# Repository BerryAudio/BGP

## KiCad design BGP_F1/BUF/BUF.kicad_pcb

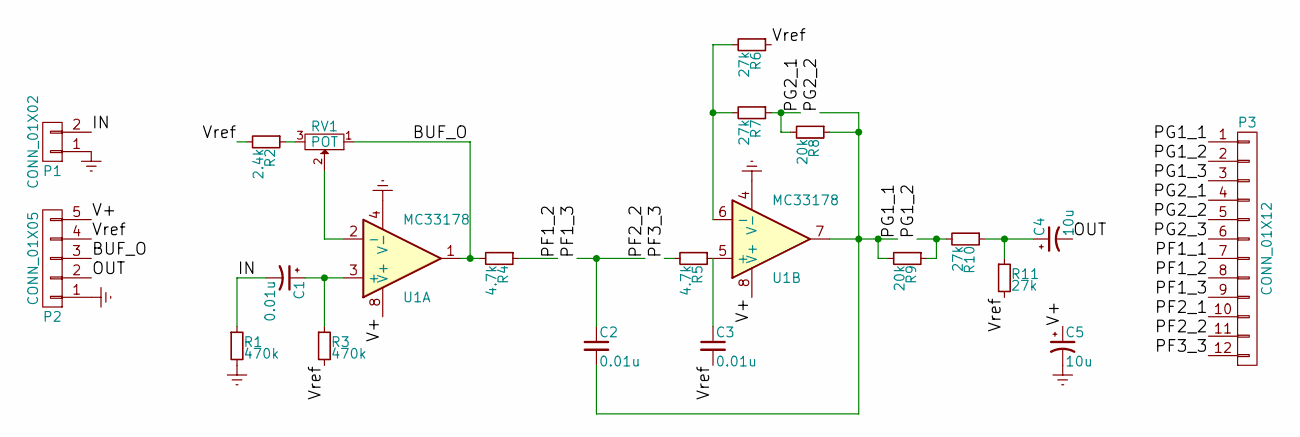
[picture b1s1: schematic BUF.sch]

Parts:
C1: 0.01u; TantalC_SizeR_EIA-2012
C2, C3: 0.01u; C_0805_HandSoldering
C4, C5: 10u; TantalC_SizeR_EIA-2012
P1: CONN_01X02; TerminalBlock_Pheonix_MPT-2.54mm_2pol
P2: CONN_01X05; JST_PH_B5B-PH-K_05x2.00mm_Straight
P3: CONN_01X12; Potentiometer_Alps_RK097_Quad_Vertical_Dual_Shaft
R1, R3: 470k; R_0603_HandSoldering
R2: 2.4k; R_0603_HandSoldering
R4, R5: 4.7k; R_0603_HandSoldering
R6, R7, R10, R11: 27k; R_0603_HandSoldering
R8, R9: 20k; R_0603_HandSoldering
RV1: POT; Potentiometer_Trimmer_Bourns_3296X
U1: MC33178; SOIC-8_3.9x4.9mm_Pitch1.27mm

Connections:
/BUF_O: P2.3, R4.2, RV1.1, U1.1
/IN: C1.2, P1.2, R1.1
/OUT: C4.2, P2.2
/PF1_1: P3.7
/PF1_2: P3.8, R4.1
/PF1_3: C2.1, P3.9, P3.11
/PF2_1: P3.10
/PF3_3: P3.12, R5.2
/PG1_1: C2.2, P3.1, P3.5, R8.1, R9.2, U1.7
/PG1_2: P3.2, R9.1, R10.2
/PG1_3: P3.3
/PG2_1: P3.4, R7.1, R8.2
/PG2_3: P3.6
/V+: C5.1, P2.5, U1.8 (V+)
/Vref: C3.2, P2.4, R2.2, R3.2, R6.1, R11.2
Earth: C5.2, P1.1, P2.1, R1.2, U1.4 (V-)
unnamed: C1.1, R3.1, U1.3 (+)
unnamed: C3.1, R5.1, U1.5 (+)
unnamed: C4.1, R10.1, R11.1
unnamed: R2.1, RV1.3
unnamed: R6.2, R7.2, U1.6 (-)
unnamed: RV1.2, U1.2 (-)

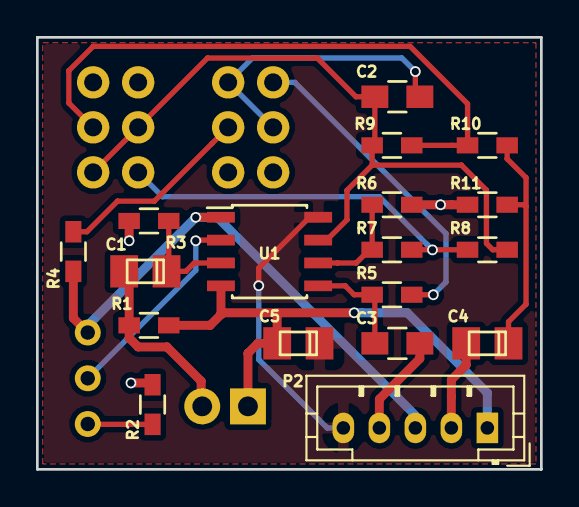
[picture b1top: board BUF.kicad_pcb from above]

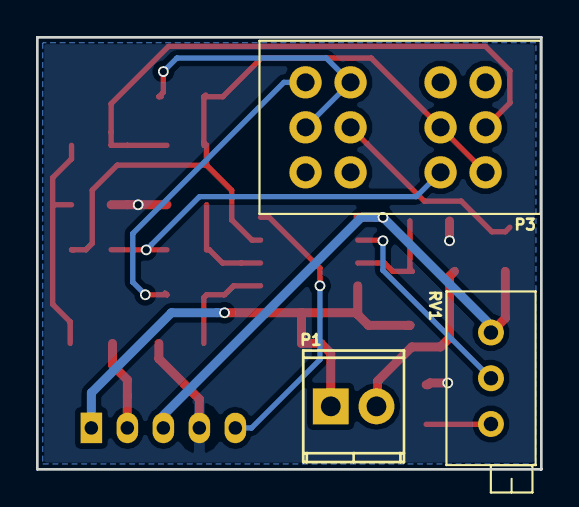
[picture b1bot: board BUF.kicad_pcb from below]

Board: 2 copper layers, 28.0 x 24.0 mm, 21 parts (3 on the bottom side), 18 nets.

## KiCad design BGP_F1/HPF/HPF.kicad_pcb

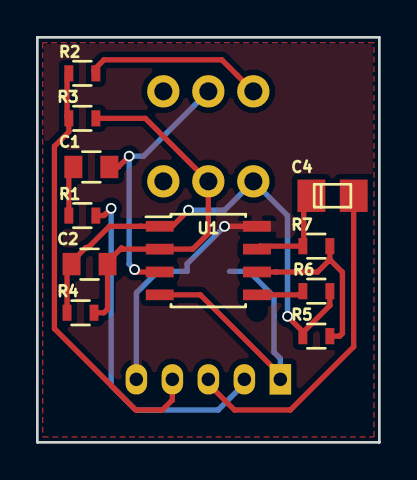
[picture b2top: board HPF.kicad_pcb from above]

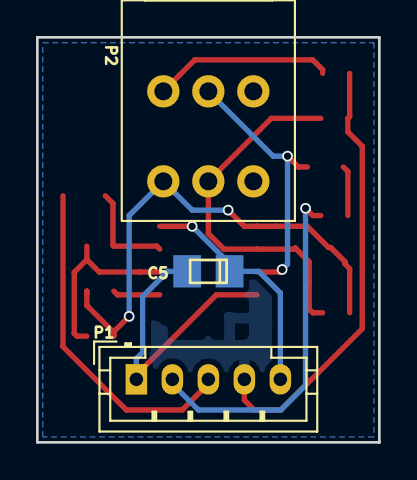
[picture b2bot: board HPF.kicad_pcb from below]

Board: 2 copper layers, 19.0 x 22.5 mm, 14 parts (3 on the bottom side), 13 nets.

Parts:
C1: 2.7n; C_0805
C2: 100p; C_0805
C4, C5: 10u; TantalC_SizeR_EIA-2012
P1: CONN_01X05; JST_PH_B5B-PH-K_05x2.00mm_Straight
P2: CONN_01X06; Potentiometer_Alps_RK097_Double_Vertical_Dual_Shaft
R1: 100; R_0603
R2: 10k; R_0603
R3, R5, R7: 4.7k; R_0603
R4: 24k; R_0603
R6: 47k; R_0603
U1: MC33178; SOIC-8_3.9x4.9mm_Pitch1.27mm

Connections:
/BUF_I: P1.2, R1.2
/OUT: C4.2, P1.3
/V+: C5.1, P1.5, U1.8
/VF_2: C1.1, P2.2, U1.3
/VF_3: P2.3, R2.2
/VG_2: C2.2, P2.5, R3.2, R4.2, U1.2
/VG_3: C2.1, P2.6, R4.1, R5.2, R6.2, U1.1
/Vref: P1.4, R2.1, R3.1
Earth: C5.2, P1.1, U1.4
unnamed: C1.2, R1.1
unnamed: R6.1, U1.5
unnamed: C4.1, R7.1, U1.7
unnamed: R5.1, R7.2, U1.6

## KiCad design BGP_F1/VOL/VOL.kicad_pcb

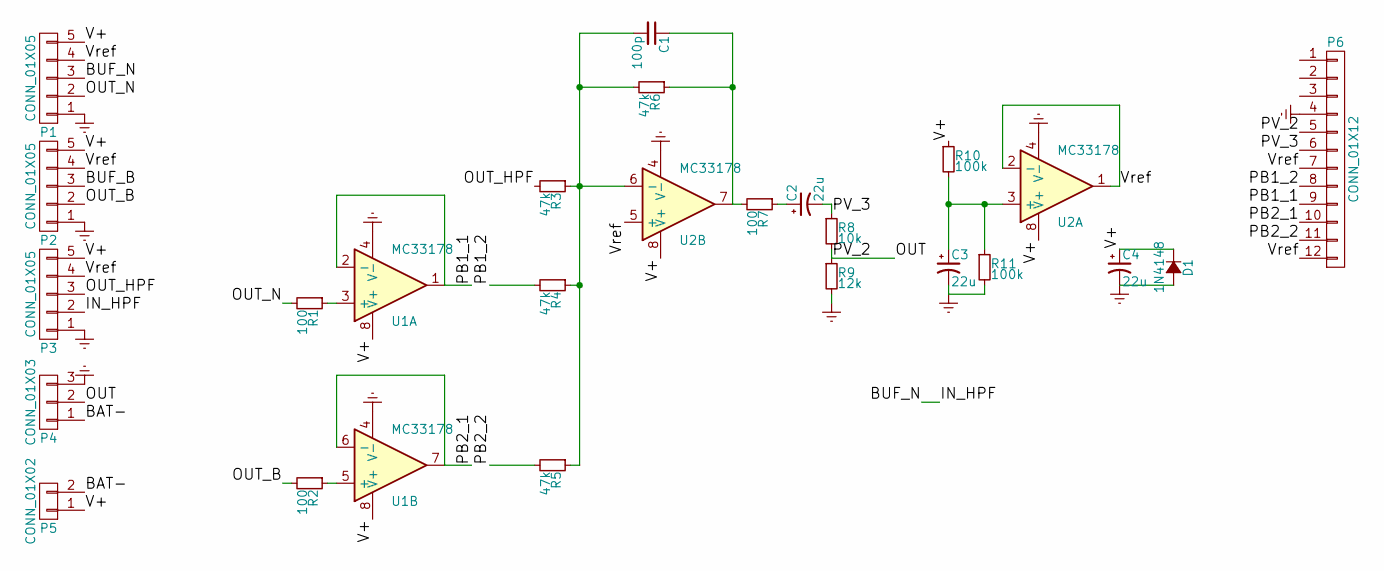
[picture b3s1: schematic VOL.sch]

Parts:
C1: 100p; C_0805
C2, C3, C4: 22u; TantalC_SizeS_EIA-3216
D1: 1N4148; SOD-123
P1: CONN_01X05; SMA_Standard
P2, P3: CONN_01X05; JST_PH_B5B-PH-K_05x2.00mm_Straight
P4: CONN_01X03; TerminalBlock_Pheonix_MPT-2.54mm_3pol
P5: CONN_01X02; TerminalBlock_Pheonix_MPT-2.54mm_2pol
P6: CONN_01X12; Potentiometer_Alps_RK097_Quad_Vertical_Dual_Shaft
R1, R2, R7: 100; R_0603
R3, R4, R5, R6: 47k; R_0603
R8: 10k; R_0603
R9: 12k; R_0603
R10, R11: 100k; R_0603
U1, U2: MC33178; SOIC-8_3.9x4.9mm_Pitch1.27mm

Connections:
/BAT-: P4.1, P5.2
/BUF_B: P2.3
/BUF_N: P1.3, P3.2
/OUT: P4.2, P6.5, R8.2, R9.1
/OUT_B: P2.2, R2.2
/OUT_HPF: P3.3, R3.2
/OUT_N: P1.2, R1.2
/PB1_1: P6.9, U1.1, U1.2 (-)
/PB1_2: P6.8, R4.2
/PB2_1: P6.10, U1.6 (-), U1.7
/PB2_2: P6.11, R5.2
/PV_3: C2.2, P6.6, R8.1
/V+: C4.1, D1.1 (K), P1.5, P2.5, P3.5, P5.1, R10.1, U1.8 (V+), U2.8 (V+)
/Vref: P1.4, P2.4, P3.4, P6.7, P6.12, U2.1, U2.2 (-), U2.5 (+)
Earth: C3.2, C4.2, D1.2 (A), P1.1, P2.1, P3.1, P4.3, P6.4, R9.2, R11.2, U1.4 (V-), U2.4 (V-)
unnamed: C1.1, R6.1, R7.2, U2.7
unnamed: C1.2, R3.1, R4.1, R5.1, R6.2, U2.6 (-)
unnamed: C2.1, R7.1
unnamed: C3.1, R10.2, R11.1, U2.3 (+)
unnamed: R1.1, U1.3 (+)
unnamed: R2.1, U1.5 (+)

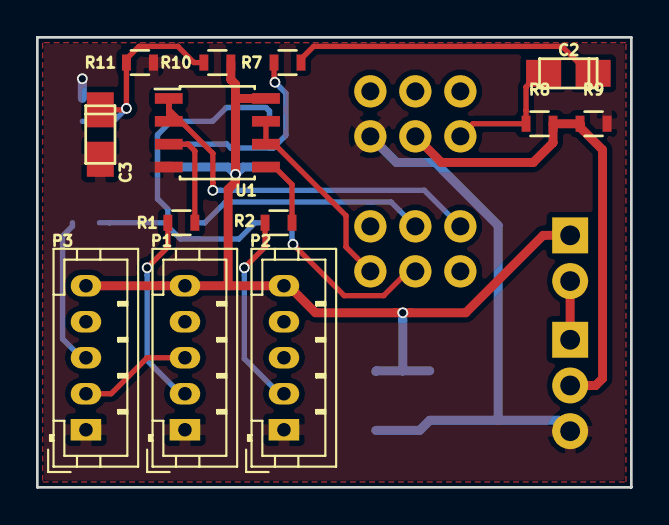
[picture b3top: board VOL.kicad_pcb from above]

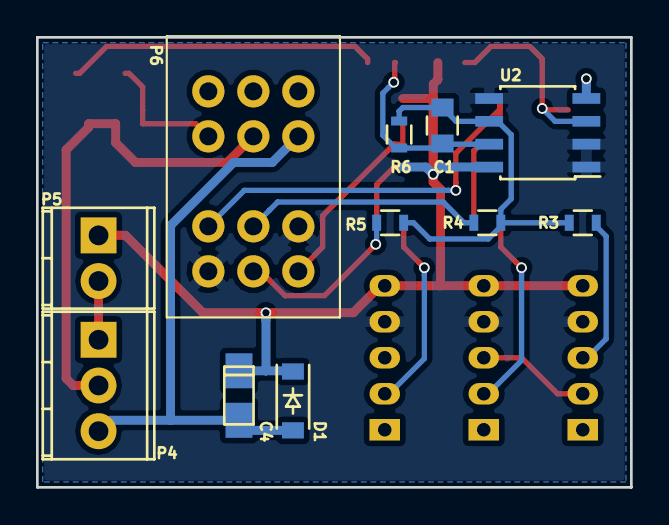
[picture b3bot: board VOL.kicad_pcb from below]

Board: 2 copper layers, 33.0 x 25.0 mm, 24 parts (11 on the bottom side), 20 nets.

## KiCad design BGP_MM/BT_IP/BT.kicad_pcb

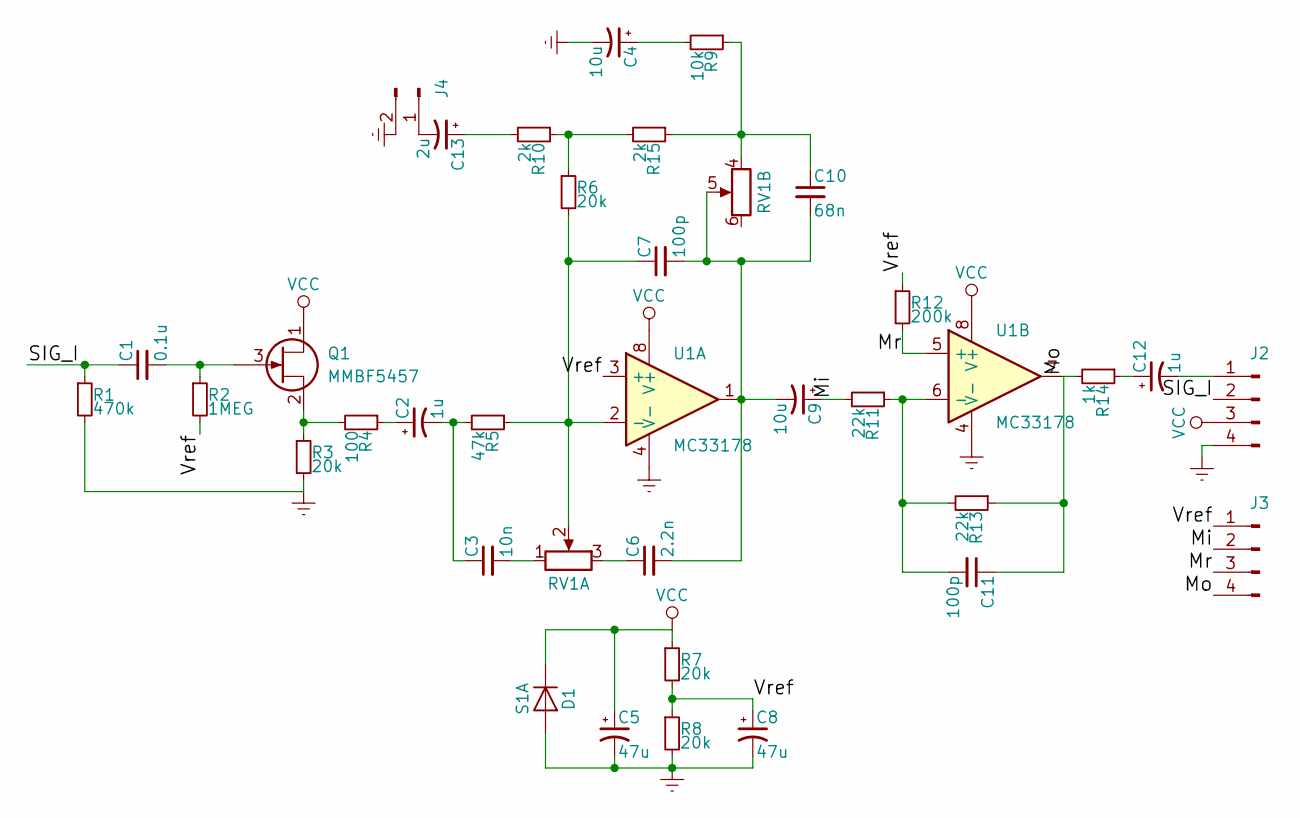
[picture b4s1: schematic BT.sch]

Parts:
C1: 0.1u; C_0805
C2, C12: 1u; C_0805
C3: 10n; C_Rect_L4.6mm_W3.0mm_P2.50mm_MKS02_FKP02
C4: 10u; C_1206_HandSoldering
C5: 47u; C_1206_HandSoldering
C6: 2.2n; C_0805
C7, C11: 100p; C_0603
C8: 47u; C_1206
C9: 10u; C_1206
C10: 68n; C_Rect_L4.6mm_W3.0mm_P2.50mm_MKS02_FKP02
C13: 2u; C_0805
D1: S1A; D_SMA
J2, J3: Conn_01x04_Male; JST_PH_B4B-PH-K_04x2.00mm_Straight
J4: Conn_01x02_Male; JST_PH_B2B-PH-K_02x2.00mm_Straight
Q1: MMBF5457; SOT-23
R1: 470k; R_0603
R2: 1MEG; R_0603
R3, R6, R7, R8: 20k; R_0603
R4: 100; R_0603
R5: 47k; R_0603
R9: 10k; R_0603
R10, R15: 2k; R_0603
R11, R13: 22k; R_0603
R12: 200k; R_0603
R14: 1k; R_0603
RV1: POT_MM_DUAL; Potentiometer_Alpha_Double_Vertical_Dual_Shaft
U1: MC33178; SOIC-8-N

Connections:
/Mi: C9.1, J3.2, R11.2
/Mo: C11.1, J3.4, R13.1, R14.2, U1.7
/Mr: J3.3, R12.2, U1.5 (+)
/SIG_I: C1.1, J2.2, R1.1
/Vref: C8.1, J3.1, R2.2, R7.2, R8.1, R12.1, U1.3 (+)
Earth: C4.2, C5.2, C8.2, D1.2 (A), J2.4, J4.2, R1.2, R3.2, R8.2, U1.4 (V-)
unnamed: C1.2, Q1.3 (G), R2.1
unnamed: C2.1, R4.1
unnamed: C2.2, C3.1, R5.2
unnamed: C3.2, RV1.1 (4)
unnamed: C4.1, R9.2
unnamed: C6.1, RV1.3 (6)
unnamed: C7.1, R5.1, R6.2, RV1.2 (5), U1.2 (-)
unnamed: C10.1, R9.1, R15.1, RV1.4
unnamed: C6.2, C7.2, C9.2, C10.2, RV1.5, U1.1
unnamed: C11.2, R11.1, R13.2, U1.6 (-)
unnamed: C12.1, R14.1
unnamed: C12.2, J2.1
unnamed: C13.1, R10.2
unnamed: C13.2, J4.1
unnamed: Q1.2 (S), R3.1, R4.2
unnamed: R6.1, R10.1, R15.2
VCC: C5.1, D1.1 (K), J2.3, Q1.1 (D), R7.1, U1.8 (V+)

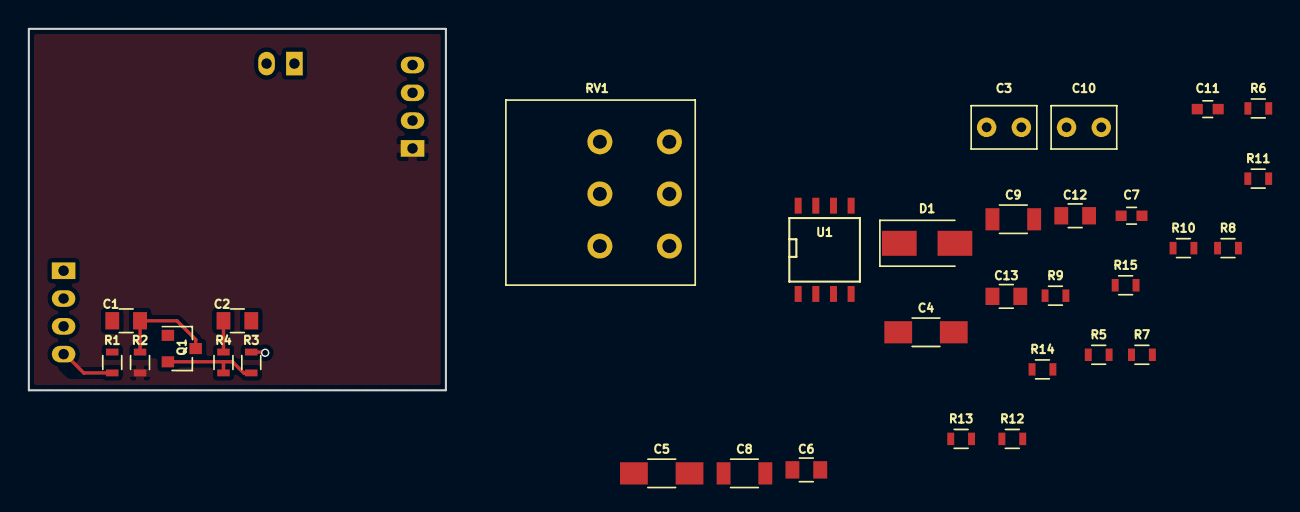
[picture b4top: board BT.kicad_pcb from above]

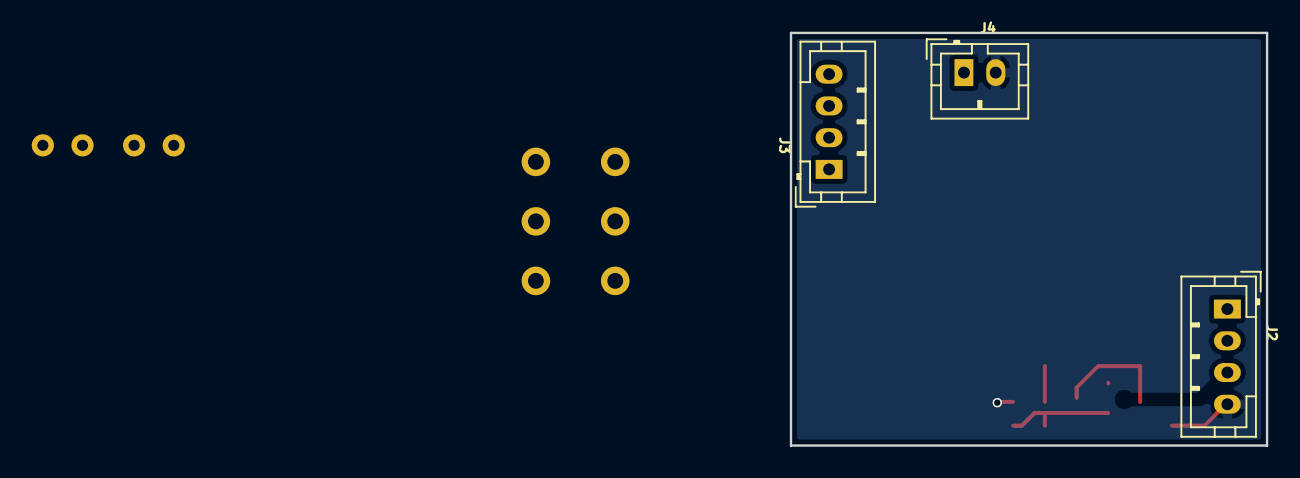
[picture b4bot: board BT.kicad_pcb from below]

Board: 2 copper layers, 30.0 x 26.0 mm, 35 parts (3 on the bottom side), 23 nets.

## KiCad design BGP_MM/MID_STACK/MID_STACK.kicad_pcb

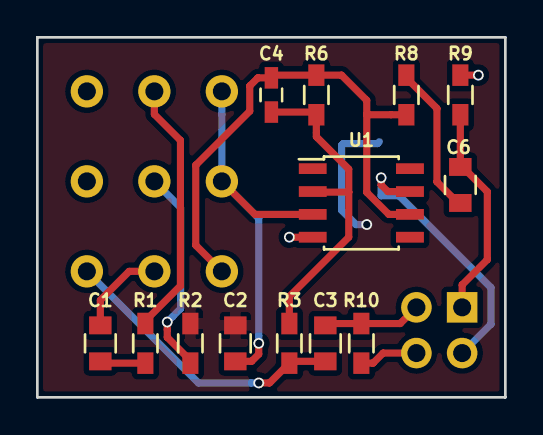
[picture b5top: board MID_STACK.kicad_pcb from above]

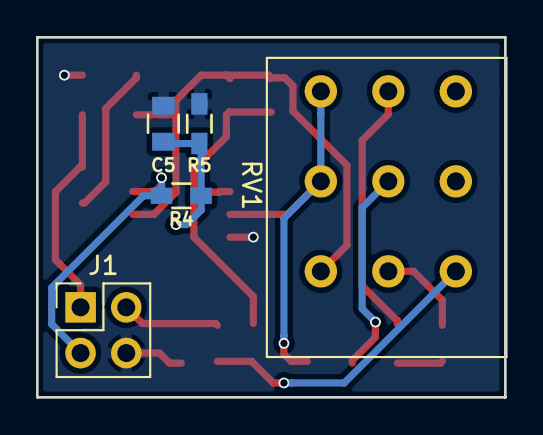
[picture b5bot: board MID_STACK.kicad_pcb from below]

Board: 2 copper layers, 26.0 x 20.0 mm, 18 parts (5 on the bottom side), 14 nets.

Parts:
C1: 10n; C_0805
C2: 4.7n; C_0805
C3, C5, C6: 10u; C_0805
C4: 120p; C_0603_HandSoldering
J1: Conn_01x04_Male; Pin_Header_Straight_2x02_Pitch2.54mm
R1, R2: 10k; R_0603_HandSoldering
R3, R6: 20k; R_0603_HandSoldering
R4, R5, R9, R10: 100k; R_0603_HandSoldering
R8: 1k; R_0603_HandSoldering
RV1: CONN_01X09; Potentiometer_Alpha_Tripple_Vertical_Dual_Shaft
U1: TL061; SOIC-8_3.9x4.9mm_Pitch1.27mm

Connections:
/F1_2: R1.2, RV1.2
/F2_2: R2.1, RV1.5
/IN: C3.2, J1.2, R10.1
/MID_I: C3.1, R3.1, RV1.7
/MID_O: C4.1, R6.2, R8.1, RV1.9, U1.6
/MID_R: C2.1, RV1.3, RV1.6, U1.3
/OUT: C6.2, J1.1, R9.1
/VOL2: C1.1, RV1.8
/Vref: C2.2, C5.1, R2.2, R4.2, R5.1
Earth: C5.2, J1.4, R5.2, R9.2, R10.2, U1.4
unnamed: C1.2, R1.1
unnamed: C4.2, R3.2, R6.1, U1.2
unnamed: C6.1, R8.2
VCC: J1.3, R4.1, U1.7

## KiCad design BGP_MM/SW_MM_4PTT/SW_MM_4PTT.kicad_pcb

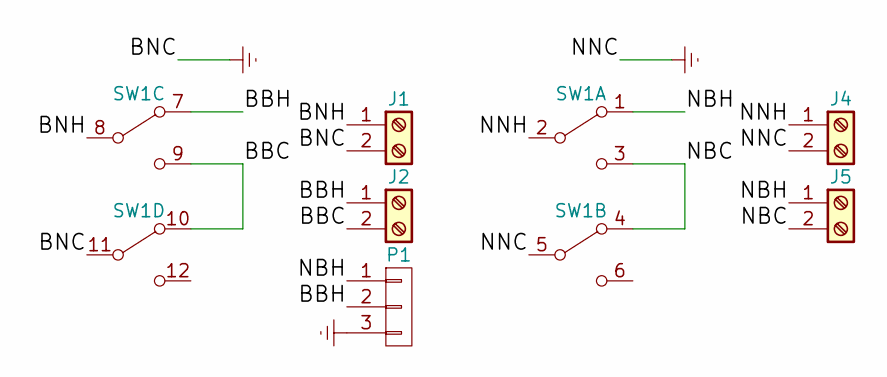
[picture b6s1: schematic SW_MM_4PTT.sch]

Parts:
J1, J2, J4, J5: Screw_Terminal_01x02; TerminalBlock_Phoenix_MPT-2.54mm_2pol
P1: CONN_01X03; JST_PH_B3B-PH-K_03x2.00mm_Straight
SW1: SW_4PDT_x4; NKK_DP3T

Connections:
/BBC: J2.2, SW1.9 (C), SW1.10 (A)
/BBH: J2.1, P1.2, SW1.7 (A)
/BNH: J1.1, SW1.8 (B)
/NBC: J5.2, SW1.3 (C), SW1.4 (A)
/NBH: J5.1, P1.1, SW1.1 (A)
/NNH: J4.1, SW1.2 (B)
Earth: J1.2, J4.2, P1.3, SW1.5 (B), SW1.11 (B)

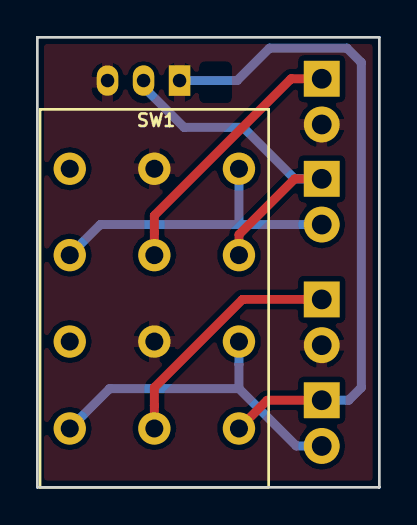
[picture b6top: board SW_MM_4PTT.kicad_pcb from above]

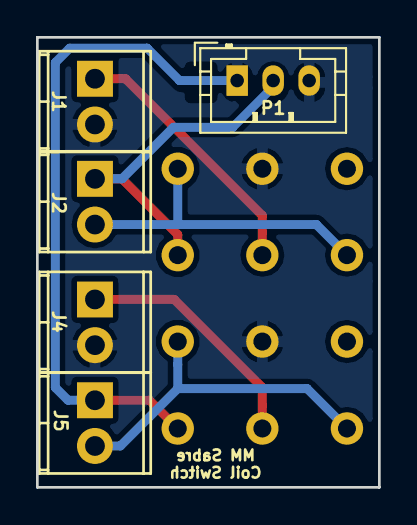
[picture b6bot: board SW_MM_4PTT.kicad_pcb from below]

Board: 2 copper layers, 19.0 x 25.0 mm, 6 parts (5 on the bottom side), 7 nets.

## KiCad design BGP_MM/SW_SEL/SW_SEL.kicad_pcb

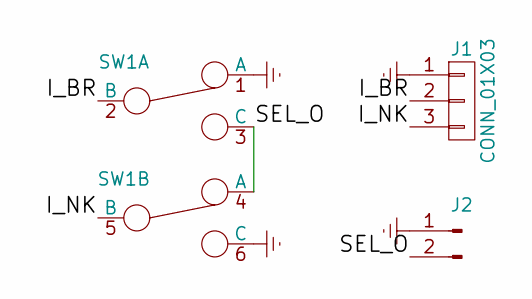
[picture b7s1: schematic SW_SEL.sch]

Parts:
J1: CONN_01X03; JST_PH_B3B-PH-K_03x2.00mm_Straight
J2: Conn_01x02_Male; JST_PH_B2B-PH-K_02x2.00mm_Straight
SW1: Switch_SPDT_x2; NKK_DPDT

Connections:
/I_BR: J1.2, SW1.2 (B)
/I_NK: J1.3, SW1.5 (B)
/SEL_O: J2.2, SW1.3 (C), SW1.4 (A)
Earth: J1.1, J2.1, SW1.1 (A), SW1.6 (C)

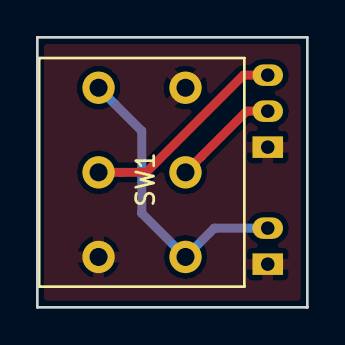
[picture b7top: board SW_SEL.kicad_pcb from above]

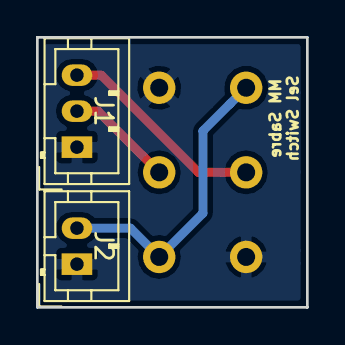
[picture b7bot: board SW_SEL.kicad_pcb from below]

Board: 2 copper layers, 15.0 x 15.0 mm, 3 parts (2 on the bottom side), 4 nets.
